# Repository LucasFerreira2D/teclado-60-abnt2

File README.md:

# Teclado 60% ABNT2 com fileira F

Teclado mecânico próprio: layout **60% ABNT2 com fileira de funções** (76 teclas), switches **hot-swap**,
**RGB por tecla + underglow + iluminação lateral**, **knob** e conector para **OLED**. O cérebro é uma
**Black Pill STM32F411** encaixada num soquete no verso da placa, pensada para rodar **QMK**.

A placa foi feita no **KiCad 10** quase toda **por script** (posicionamento, roteamento, acabamento e
correções), sem desenhar à mão no editor. Os scripts estão em [`hardware/tools/`](hardware/tools).

> **Status:** projeto da placa concluído e revisado (DRC sem erros), **ainda não fabricado**. Firmware QMK
> ainda não escrito. Pendências em [Antes de fabricar](#antes-de-fabricar).

---

## Conceito

Como o teclado deve ficar montado (esboço 3D feito antes da placa; o case ainda não existe):

| Lateral | Lateral em 3/4 |
|---|---|
|  |  |

Na lateral aparecem a cunha do case, o rasgo de RGB na altura da placa e o underglow na mesa.

- **Case em cunha** com 6° de inclinação, fechado nas laterais, e **moldura superior** que abre janelas só em
  volta de cada grupo de teclas (Esc, F1–F4, F5–F8, F9–F12, bloco principal).
- **OLED** à esquerda e **knob** à direita, na faixa acima da fileira F, rentes à moldura.
- Keycaps **perfil Cherry**, com acentos em Esc e Enter.
- **Underglow** por baixo e **rasgo de RGB nas laterais**, na altura da placa, com acrílico fosco por dentro.
- Pés traseiros dobráveis em 2 níveis.

---

## Layout

- 76 teclas: alfanumérico ABNT2 completo (`Ç`, `´`, `~`, `[`, `]`, `\`, `;`, `/`) + Esc e F1–F12.
- Enter ISO, Shift esquerdo curto (1,25u) por causa da tecla `\`.
- Sem setas nem coluna de navegação (não é 65%): setas, Del, Home/End e afins ficam numa camada no `Fn`.
- Fonte do layout: [`hardware/layout/teclado-kle.json`](hardware/layout/teclado-kle.json). Abra em
  [keyboard-layout-editor.com](http://www.keyboard-layout-editor.com) (*Raw data* → colar).

## A placa

| Frente | Verso |
|---|---|
|  |  |

Roteamento (vermelho = frente, azul = verso + plano de GND), com o acabamento das trilhas em retas e 45°:

### Especificações

| Item | Detalhe |
|---|---|
| Placa | 292 × 143 mm, 2 camadas, 1,6 mm, cantos com raio de 3 mm |
| Fixação | 10 furos M2 |
| Matriz | 6 linhas × 14 colunas, diodo 1N4148W (SOD-123) por tecla, catodo na linha |
| Switches | Cherry MX e compatíveis, soquete **Kailh hot-swap** (sem solda) |
| Estabilizadores | Cherry MX de placa: 2u (Backspace, Enter) e 6,25u (Espaço) |
| Microcontrolador | **WeAct Black Pill V3.x (STM32F411)** num soquete DIP-40, no verso |
| USB | USB-C (HRO TYPE-C-31-M-12), resistores CC de 5,1k, ESD USBLC6-2SC6, fusível de 500 mA |
| Knob | Encoder EC11 com clique (o clique entra na matriz em ROW0 × COL13) |
| Tela | Conector de 4 pinos para OLED I²C (GND, VCC, SCL, SDA) |

### Iluminação (102 LEDs endereçáveis numa cadeia só)

| Grupo | LEDs | Peça |
|---|---|---|
| Por tecla | LED1–LED76 | SK6812MINI-E, montagem reversa (brilha através do switch) |
| Underglow | LED101–LED114 | 14× SK6812MINI no verso, virados para a mesa |
| Laterais | LED201–LED212 | 12× SK6812SIDE-A na borda, apontando para fora |

Cada LED tem o próprio capacitor de 100 nF. O sinal de dados sai do STM32 (3,3 V) e passa por um
**74AHCT1G125**, que converte para 5 V antes de entrar na cadeia.

### Pinos da Black Pill usados

| Função | Pino |
|---|---|
| Dados do RGB | PA8 |
| OLED (I²C) | PB6 (SCL), PB7 (SDA) |
| Knob (A/B) | PA0, PA1 |

O mapa completo de linhas e colunas está no esquemático ([`hardware/teclado.pdf`](hardware/teclado.pdf)).

## Estrutura do repositório

```
hardware/
├── teclado.kicad_pro / .kicad_sch / .kicad_pcb   projeto KiCad 10 (abra o .kicad_pro)
├── matriz.kicad_sch, mcu.kicad_sch,
│   leds.kicad_sch, leds_extra.kicad_sch           folhas do esquemático
├── teclado.kicad_dru                              regras de DRC próprias (LED reverso, alívio térmico)
├── teclado.kicad_sym, teclado.pretty/             símbolo e footprint próprios (LED lateral)
├── teclado.pdf                                    esquemático em PDF
├── layout/teclado-kle.json                        layout no formato KLE
├── tools/                                         scripts que geraram a placa
└── REVISAO.md                                     revisão antes de fabricar
docs/img/                                          imagens deste README (geradas pelo kicad-cli)
```

## Como a placa foi feita

O fluxo inteiro roda pelo Python do KiCad (`C:\Program Files\KiCad\10.0\bin\python.exe`) e pelo
`kicad-cli`, com o KiCad fechado:

1. **Esquemático:** matriz e LEDs por teclas gerados pelo [kbplacer](https://github.com/adamws/kicad-kbplacer)
   a partir do KLE (`kbplacer.py`, `import_kbplacer.py`); folha do MCU (`gen_mcu_sheet.py`) e dos LEDs
   extras (`gen_leds_extra.py`) gerados por script.
2. **Placa:** contorno (`new_board.py`), sincronização com o esquemático sem abrir o editor (`sync_pcb.py`),
   posicionamento de switches, diodos, LEDs e estabilizadores pelo KLE (`place_keys.py`), eletrônica da faixa
   superior (`place_strip.py`), LEDs extras (`place_extra_leds.py`) e furação (`place_holes.py`).
3. **Roteamento:** exportação para o [FreeRouting](https://github.com/freerouting/freerouting) sem os planos
   de GND (`export_dsn.py`), importação do resultado e criação dos planos (`post_route.py`), fechamento das
   ligações que sobraram (`route_rest.py`, `open_pairs.py`).
4. **Acabamento:** trilhas em retas + 45° mantendo as mesmas pontas (`align45.py`), correções de DRC
   (`fix_drc.py`), ilhas de GND (`gnd_islands.py`) e costura dos planos com vias (`stitch_gnd.py`).

## Antes de fabricar

Resumo de [`hardware/REVISAO.md`](hardware/REVISAO.md):

- **OLED:** conferir a ordem dos pinos do módulo comprado (o header é GND-VCC-SCL-SDA). Invertido, o módulo
  cai em cima do USB-C.
- **LED lateral:** o footprint foi feito à mão. As funções dos pinos batem com o datasheet; o lado físico
  (espelhamento) ainda não foi confirmado.
- **Corrente:** 102 LEDs em branco total puxam ~3,7 A, e o fusível é de 500 mA. O firmware **precisa**
  limitar o brilho (~10% em branco, ~30% em efeitos coloridos).
- **Black Pill no verso:** o soquete com o módulo ocupa ~12–14 mm abaixo da placa (o case precisa dessa
  folga), e os botões BOOT0/NRST ficam para baixo: fazer a primeira gravação antes de fechar o case.
  Nunca ligar o USB do módulo e o da placa ao mesmo tempo.

## Próximos passos

- [ ] Fechar as pendências acima e gerar os Gerbers
- [ ] Fabricar e montar
- [ ] Firmware QMK (matriz, camada `Fn`, RGB com limite de corrente, knob, OLED)
- [ ] Case

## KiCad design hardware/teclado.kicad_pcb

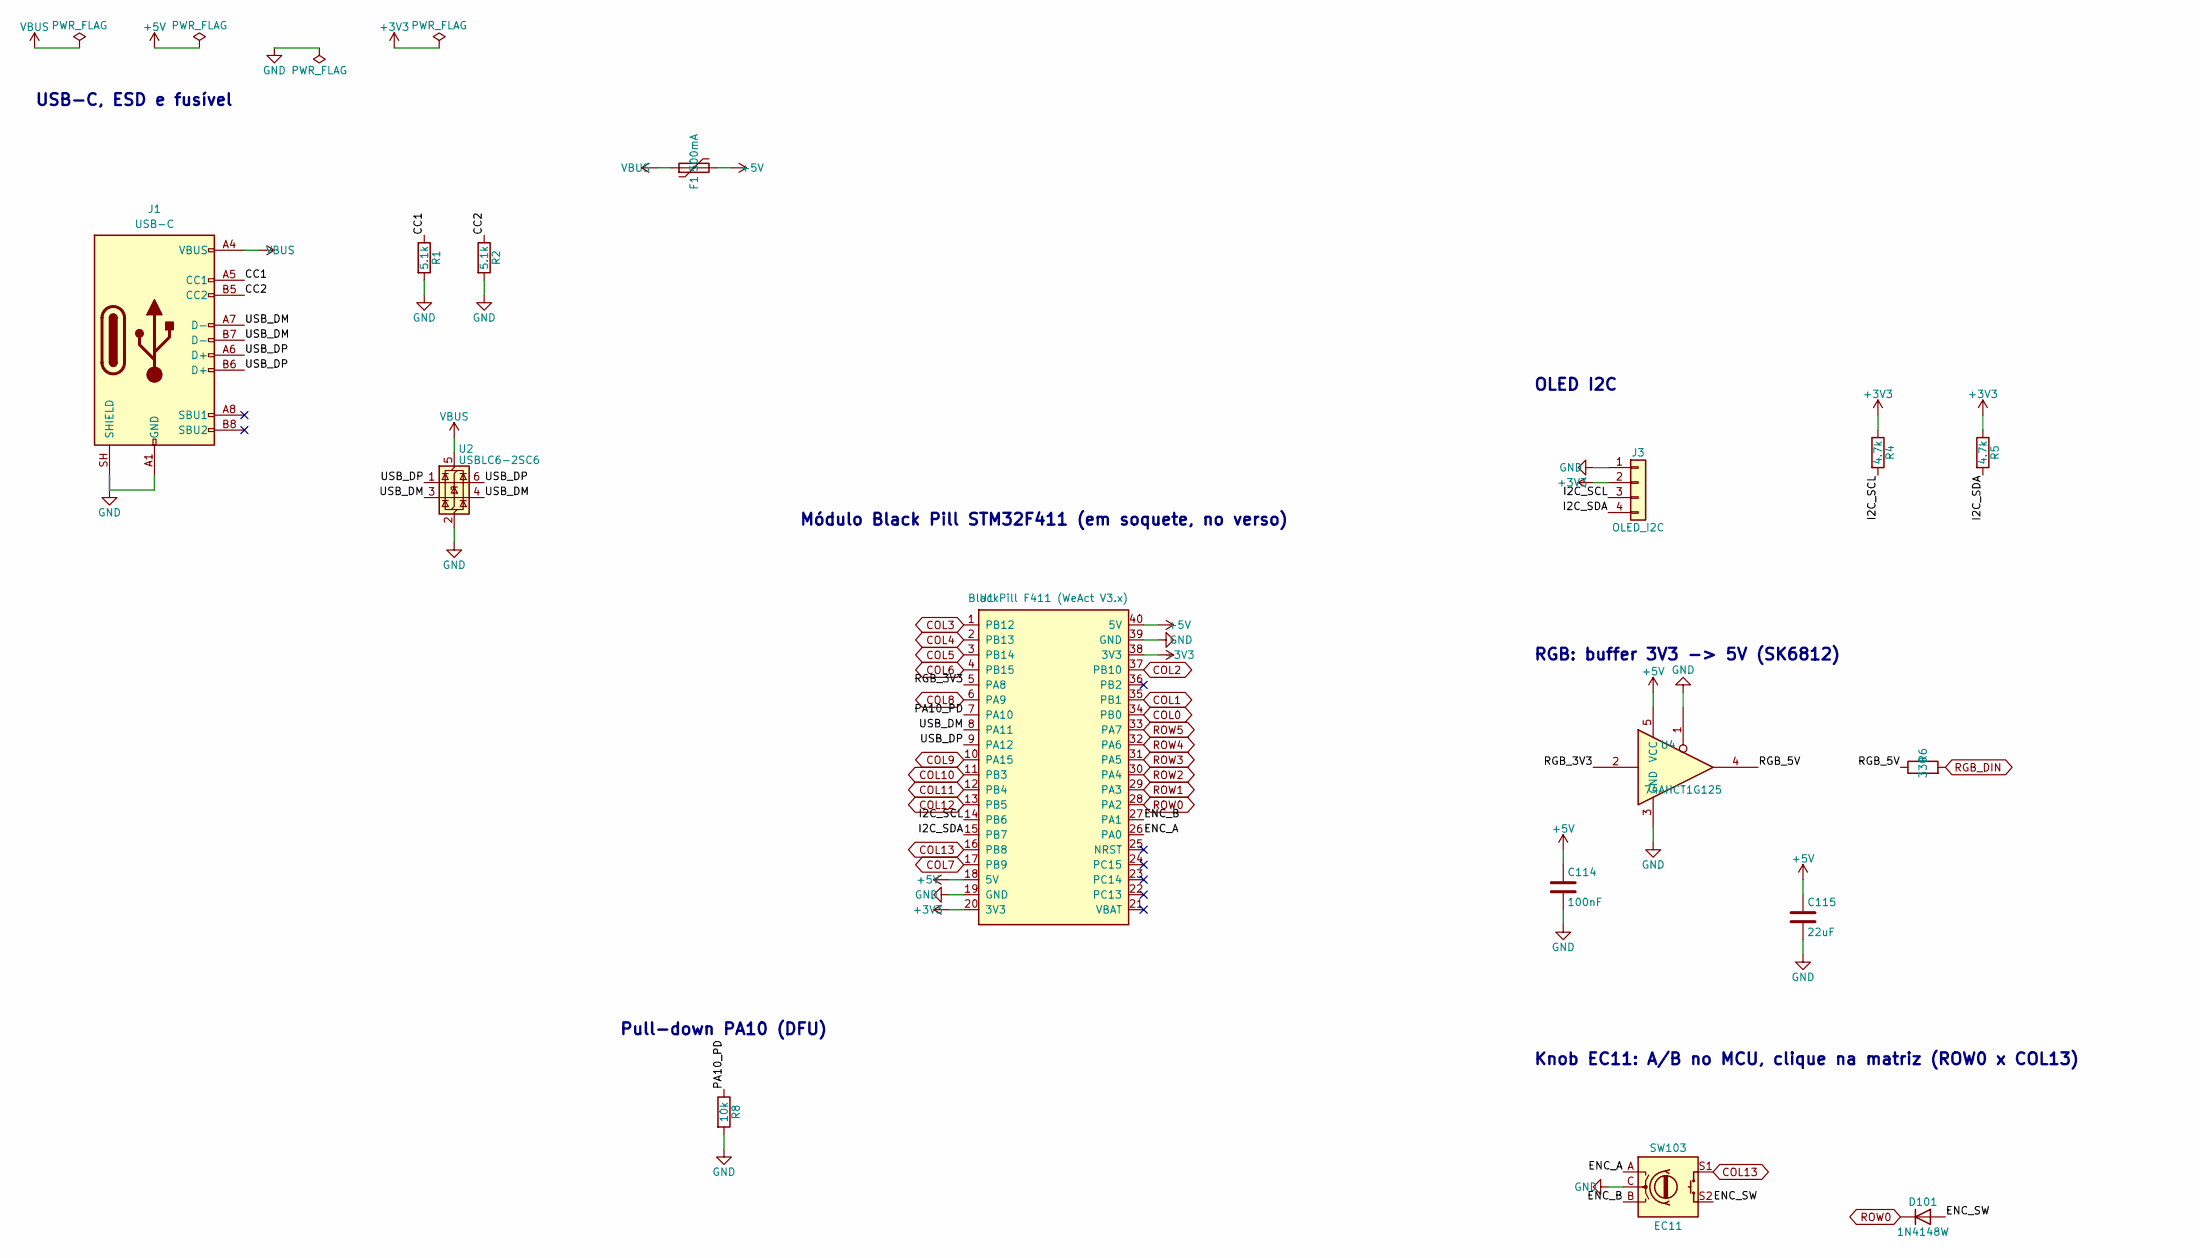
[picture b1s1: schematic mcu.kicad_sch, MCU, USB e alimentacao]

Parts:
C114: 100nF; C_0603_1608Metric
C115: 22uF; C_0805_2012Metric
D101: 1N4148W; D_SOD-123
F1: 500mA; Fuse_1206_3216Metric
J1: USB-C; USB_C_Receptacle_HRO_TYPE-C-31-M-12
J3: OLED_I2C; PinHeader_1x04_P2.54mm_Vertical
R1, R2: 5.1k; R_0603_1608Metric
R4, R5: 4.7k; R_0603_1608Metric
R6: 330; R_0603_1608Metric
R8: 10k; R_0603_1608Metric
SW103: EC11; RotaryEncoder_Alps_EC11E-Switch_Vertical_H20mm
U1: BlackPill F411 (WeAct V3.x); DIP-40_W15.24mm_Socket
U2: USBLC6-2SC6; SOT-23-6
U4: 74AHCT1G125; SOT-23-5

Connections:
+3V3: J3.2, R4.1, R5.1, U1.20 (3V3), U1.38 (3V3)
+5V: C114.1, C115.1, F1.2, U1.18 (5V), U1.40 (5V), U4.5 (VCC); also elsewhere on the board
/MCU/CC1: J1.A5 (CC1), R1.1
/MCU/CC2: J1.B5 (CC2), R2.1
/MCU/ENC_A: SW103.A, U1.26 (PA0)
/MCU/ENC_B: SW103.B, U1.27 (PA1)
/MCU/ENC_SW: D101.2 (A), SW103.S2
/MCU/I2C_SCL: J3.3, R4.2, U1.14 (PB6)
/MCU/I2C_SDA: J3.4, R5.2, U1.15 (PB7)
/MCU/PA10_PD: R8.1, U1.7 (PA10)
/MCU/RGB_3V3: U1.5 (PA8), U4.2
/MCU/RGB_5V: R6.1, U4.4
/MCU/USB_DM: J1.A7 (D-), J1.B7 (D-), U1.8 (PA11), U2.3 (I/O2), U2.4 (I/O2)
/MCU/USB_DP: J1.A6 (D+), J1.B6 (D+), U1.9 (PA12), U2.1 (I/O1), U2.6 (I/O1)
COL0: U1.34 (PB0); also elsewhere on the board
COL1: U1.35 (PB1); also elsewhere on the board
COL2: U1.37 (PB10); also elsewhere on the board
COL3: U1.1 (PB12); also elsewhere on the board
COL4: U1.2 (PB13); also elsewhere on the board
COL5: U1.3 (PB14); also elsewhere on the board
COL6: U1.4 (PB15); also elsewhere on the board
COL7: U1.17 (PB9); also elsewhere on the board
COL8: U1.6 (PA9); also elsewhere on the board
COL9: U1.10 (PA15); also elsewhere on the board
COL10: U1.11 (PB3); also elsewhere on the board
COL11: U1.12 (PB4); also elsewhere on the board
COL12: U1.13 (PB5); also elsewhere on the board
COL13: SW103.S1, U1.16 (PB8); also elsewhere on the board
GND: C114.2, C115.2, J1.A1 (GND), J1.A12 (GND), J1.B1 (GND), J1.B12 (GND), J1.SH (SHIELD), J3.1, R1.2, R2.2, R8.2, SW103.C, U1.19 (GND), U1.39 (GND), U2.2 (GND), U4.1, U4.3 (GND); also elsewhere on the board
RGB_DIN: R6.2; also elsewhere on the board
ROW0: D101.1 (K), U1.28 (PA2); also elsewhere on the board
ROW1: U1.29 (PA3); also elsewhere on the board
ROW2: U1.30 (PA4); also elsewhere on the board
ROW3: U1.31 (PA5); also elsewhere on the board
ROW4: U1.32 (PA6); also elsewhere on the board
ROW5: U1.33 (PA7); also elsewhere on the board
VBUS: F1.1, J1.A4 (VBUS), J1.A9 (VBUS), J1.B4 (VBUS), J1.B9 (VBUS), U2.5 (VBUS)

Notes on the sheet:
USB-C, ESD e fusível
Módulo Black Pill STM32F411 (em soquete, no verso)
Pull-down PA10 (DFU)
OLED I2C
RGB: buffer 3V3 -> 5V (SK6812)
Knob EC11: A/B no MCU, clique na matriz (ROW0 x COL13)

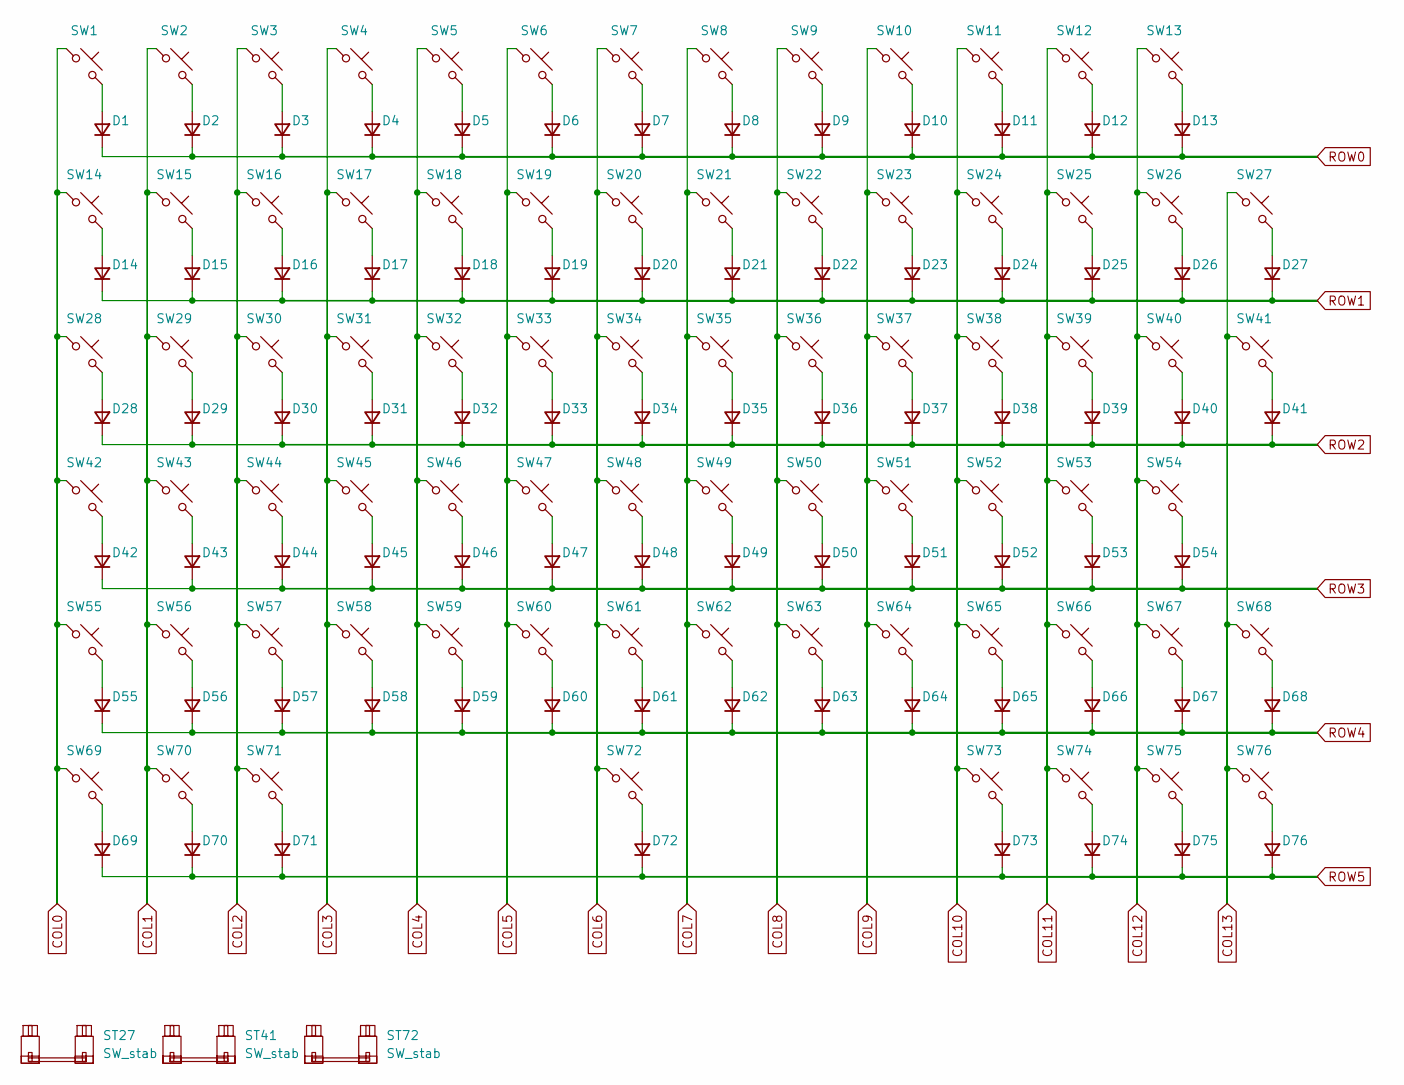
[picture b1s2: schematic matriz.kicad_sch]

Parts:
D1, D2, D3, D4, D5, D6, D7, D8, D9, D10, D11, D12, D13, D14, D15, D16, D17, D18, D19, D20, D21, D22, D23, D24, D25, D26, D27, D28, D29, D30, D31, D32, D33, D34, D35, D36, D37, D38, D39, D40, D41, D42, D43, D44, D45, D46, D47, D48, D49, D50, D51, D52, D53, D54, D55, D56, D57, D58, D59, D60, D61, D62, D63, D64, D65, D66, D67, D68, D69, D70, D71, D72, D73, D74, D75, D76: D; D_SOD-123
ST27, ST41: SW_stab; Stabilizer_Cherry_MX_2.00u
ST72: SW_stab; Stabilizer_Cherry_MX_6.25u
SW1, SW2, SW3, SW4, SW5, SW6, SW7, SW8, SW9, SW10, SW11, SW12, SW13, SW14, SW15, SW16, SW17, SW18, SW19, SW20, SW21, SW22, SW23, SW24, SW25, SW26, SW27, SW28, SW29, SW30, SW31, SW32, SW33, SW34, SW35, SW36, SW37, SW38, SW39, SW40, SW41, SW42, SW43, SW44, SW45, SW46, SW47, SW48, SW49, SW50, SW51, SW52, SW53, SW54, SW55, SW56, SW57, SW58, SW59, SW60, SW61, SW62, SW63, SW64, SW65, SW66, SW67, SW68, SW69, SW70, SW71, SW72, SW73, SW74, SW75, SW76: SW_Push; SW_Hotswap_Kailh_MX_1.00u

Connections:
COL0: SW1.1, SW14.1, SW28.1, SW42.1, SW55.1, SW69.1; also elsewhere on the board
COL1: SW2.1, SW15.1, SW29.1, SW43.1, SW56.1, SW70.1; also elsewhere on the board
COL2: SW3.1, SW16.1, SW30.1, SW44.1, SW57.1, SW71.1; also elsewhere on the board
COL3: SW4.1, SW17.1, SW31.1, SW45.1, SW58.1; also elsewhere on the board
COL4: SW5.1, SW18.1, SW32.1, SW46.1, SW59.1; also elsewhere on the board
COL5: SW6.1, SW19.1, SW33.1, SW47.1, SW60.1; also elsewhere on the board
COL6: SW7.1, SW20.1, SW34.1, SW48.1, SW61.1, SW72.1; also elsewhere on the board
COL7: SW8.1, SW21.1, SW35.1, SW49.1, SW62.1; also elsewhere on the board
COL8: SW9.1, SW22.1, SW36.1, SW50.1, SW63.1; also elsewhere on the board
COL9: SW10.1, SW23.1, SW37.1, SW51.1, SW64.1; also elsewhere on the board
COL10: SW11.1, SW24.1, SW38.1, SW52.1, SW65.1, SW73.1; also elsewhere on the board
COL11: SW12.1, SW25.1, SW39.1, SW53.1, SW66.1, SW74.1; also elsewhere on the board
COL12: SW13.1, SW26.1, SW40.1, SW54.1, SW67.1, SW75.1; also elsewhere on the board
COL13: SW27.1, SW41.1, SW68.1, SW76.1; also elsewhere on the board
unnamed: D1.2 (A), SW1.2
unnamed: D2.2 (A), SW2.2
unnamed: D3.2 (A), SW3.2
unnamed: D4.2 (A), SW4.2
unnamed: D5.2 (A), SW5.2
unnamed: D6.2 (A), SW6.2
unnamed: D7.2 (A), SW7.2
unnamed: D8.2 (A), SW8.2
unnamed: D9.2 (A), SW9.2
unnamed: D10.2 (A), SW10.2
unnamed: D11.2 (A), SW11.2
unnamed: D12.2 (A), SW12.2
unnamed: D13.2 (A), SW13.2
unnamed: D14.2 (A), SW14.2
unnamed: D15.2 (A), SW15.2
unnamed: D16.2 (A), SW16.2
unnamed: D17.2 (A), SW17.2
unnamed: D18.2 (A), SW18.2
unnamed: D19.2 (A), SW19.2
unnamed: D20.2 (A), SW20.2
unnamed: D21.2 (A), SW21.2
unnamed: D22.2 (A), SW22.2
unnamed: D23.2 (A), SW23.2
unnamed: D24.2 (A), SW24.2
unnamed: D25.2 (A), SW25.2
unnamed: D26.2 (A), SW26.2
unnamed: D27.2 (A), SW27.2
unnamed: D28.2 (A), SW28.2
unnamed: D29.2 (A), SW29.2
unnamed: D30.2 (A), SW30.2
unnamed: D31.2 (A), SW31.2
unnamed: D32.2 (A), SW32.2
unnamed: D33.2 (A), SW33.2
unnamed: D34.2 (A), SW34.2
unnamed: D35.2 (A), SW35.2
unnamed: D36.2 (A), SW36.2
unnamed: D37.2 (A), SW37.2
unnamed: D38.2 (A), SW38.2
unnamed: D39.2 (A), SW39.2
unnamed: D40.2 (A), SW40.2
unnamed: D41.2 (A), SW41.2
unnamed: D42.2 (A), SW42.2
unnamed: D43.2 (A), SW43.2
unnamed: D44.2 (A), SW44.2
unnamed: D45.2 (A), SW45.2
unnamed: D46.2 (A), SW46.2
unnamed: D47.2 (A), SW47.2
unnamed: D48.2 (A), SW48.2
unnamed: D49.2 (A), SW49.2
unnamed: D50.2 (A), SW50.2
unnamed: D51.2 (A), SW51.2
unnamed: D52.2 (A), SW52.2
unnamed: D53.2 (A), SW53.2
unnamed: D54.2 (A), SW54.2
unnamed: D55.2 (A), SW55.2
unnamed: D56.2 (A), SW56.2
unnamed: D57.2 (A), SW57.2
unnamed: D58.2 (A), SW58.2
unnamed: D59.2 (A), SW59.2
unnamed: D60.2 (A), SW60.2
unnamed: D61.2 (A), SW61.2
unnamed: D62.2 (A), SW62.2
unnamed: D63.2 (A), SW63.2
unnamed: D64.2 (A), SW64.2
unnamed: D65.2 (A), SW65.2
unnamed: D66.2 (A), SW66.2
unnamed: D67.2 (A), SW67.2
unnamed: D68.2 (A), SW68.2
unnamed: D69.2 (A), SW69.2
unnamed: D70.2 (A), SW70.2
unnamed: D71.2 (A), SW71.2
unnamed: D72.2 (A), SW72.2
unnamed: D73.2 (A), SW73.2
unnamed: D74.2 (A), SW74.2
unnamed: D75.2 (A), SW75.2
unnamed: D76.2 (A), SW76.2
ROW0: D1.1 (K), D2.1 (K), D3.1 (K), D4.1 (K), D5.1 (K), D6.1 (K), D7.1 (K), D8.1 (K), D9.1 (K), D10.1 (K), D11.1 (K), D12.1 (K), D13.1 (K); also elsewhere on the board
ROW1: D14.1 (K), D15.1 (K), D16.1 (K), D17.1 (K), D18.1 (K), D19.1 (K), D20.1 (K), D21.1 (K), D22.1 (K), D23.1 (K), D24.1 (K), D25.1 (K), D26.1 (K), D27.1 (K); also elsewhere on the board
ROW2: D28.1 (K), D29.1 (K), D30.1 (K), D31.1 (K), D32.1 (K), D33.1 (K), D34.1 (K), D35.1 (K), D36.1 (K), D37.1 (K), D38.1 (K), D39.1 (K), D40.1 (K), D41.1 (K); also elsewhere on the board
ROW3: D42.1 (K), D43.1 (K), D44.1 (K), D45.1 (K), D46.1 (K), D47.1 (K), D48.1 (K), D49.1 (K), D50.1 (K), D51.1 (K), D52.1 (K), D53.1 (K), D54.1 (K); also elsewhere on the board
ROW4: D55.1 (K), D56.1 (K), D57.1 (K), D58.1 (K), D59.1 (K), D60.1 (K), D61.1 (K), D62.1 (K), D63.1 (K), D64.1 (K), D65.1 (K), D66.1 (K), D67.1 (K), D68.1 (K); also elsewhere on the board
ROW5: D69.1 (K), D70.1 (K), D71.1 (K), D72.1 (K), D73.1 (K), D74.1 (K), D75.1 (K), D76.1 (K); also elsewhere on the board

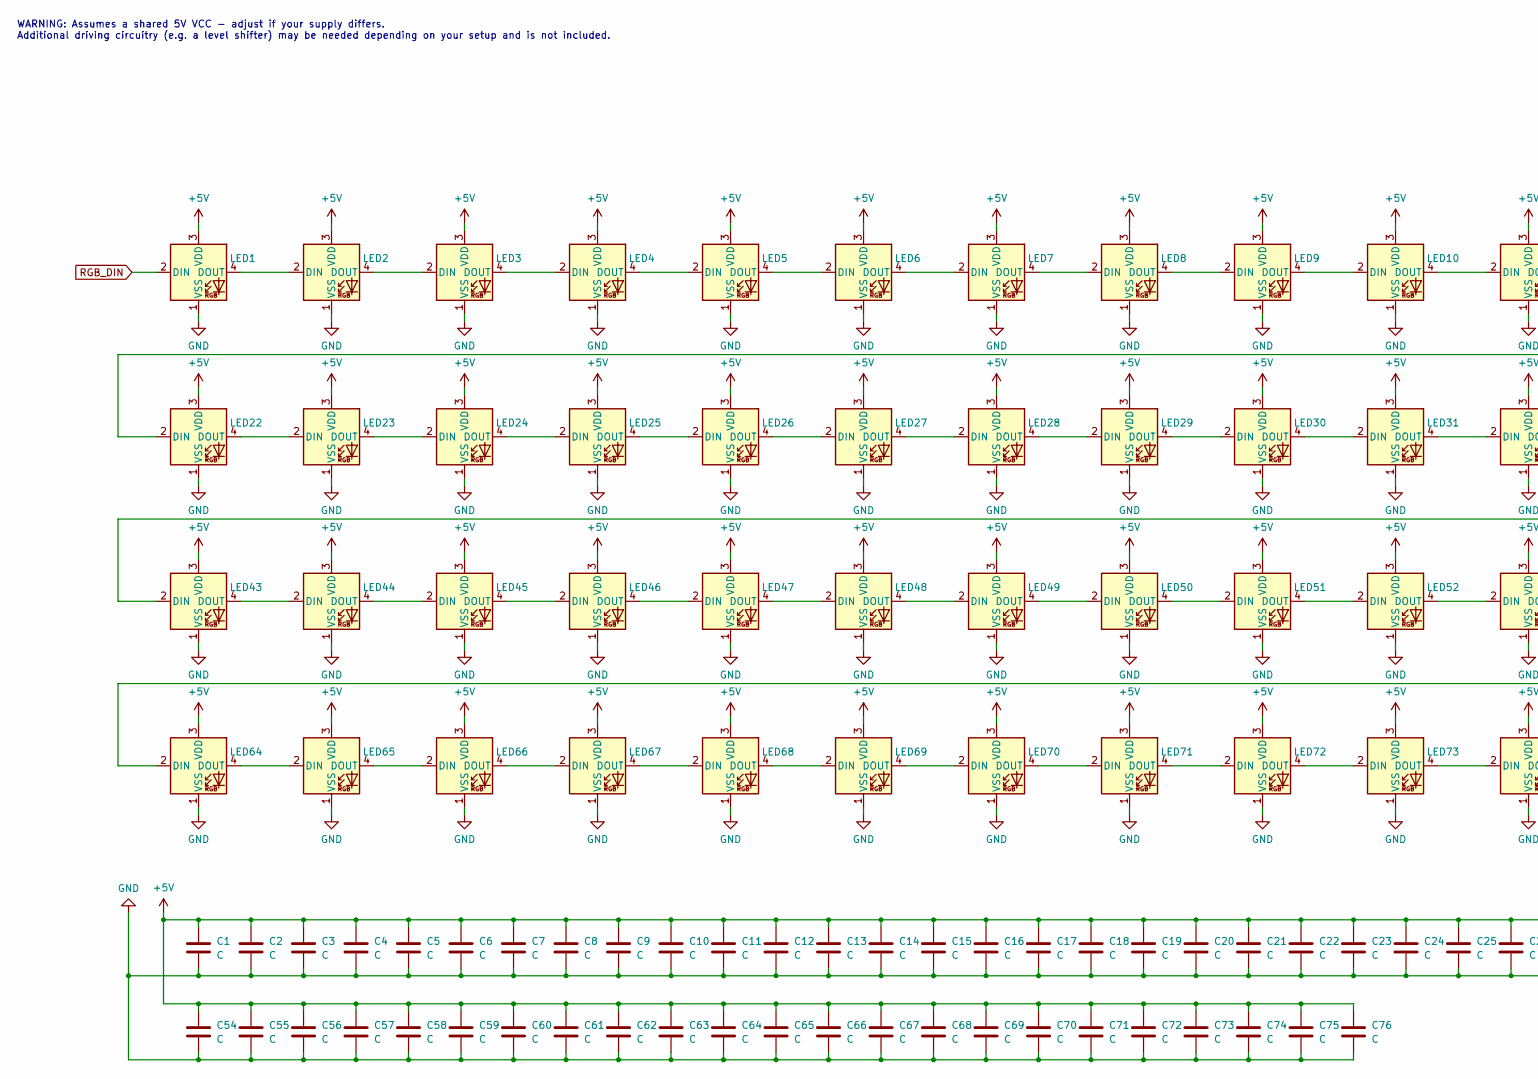
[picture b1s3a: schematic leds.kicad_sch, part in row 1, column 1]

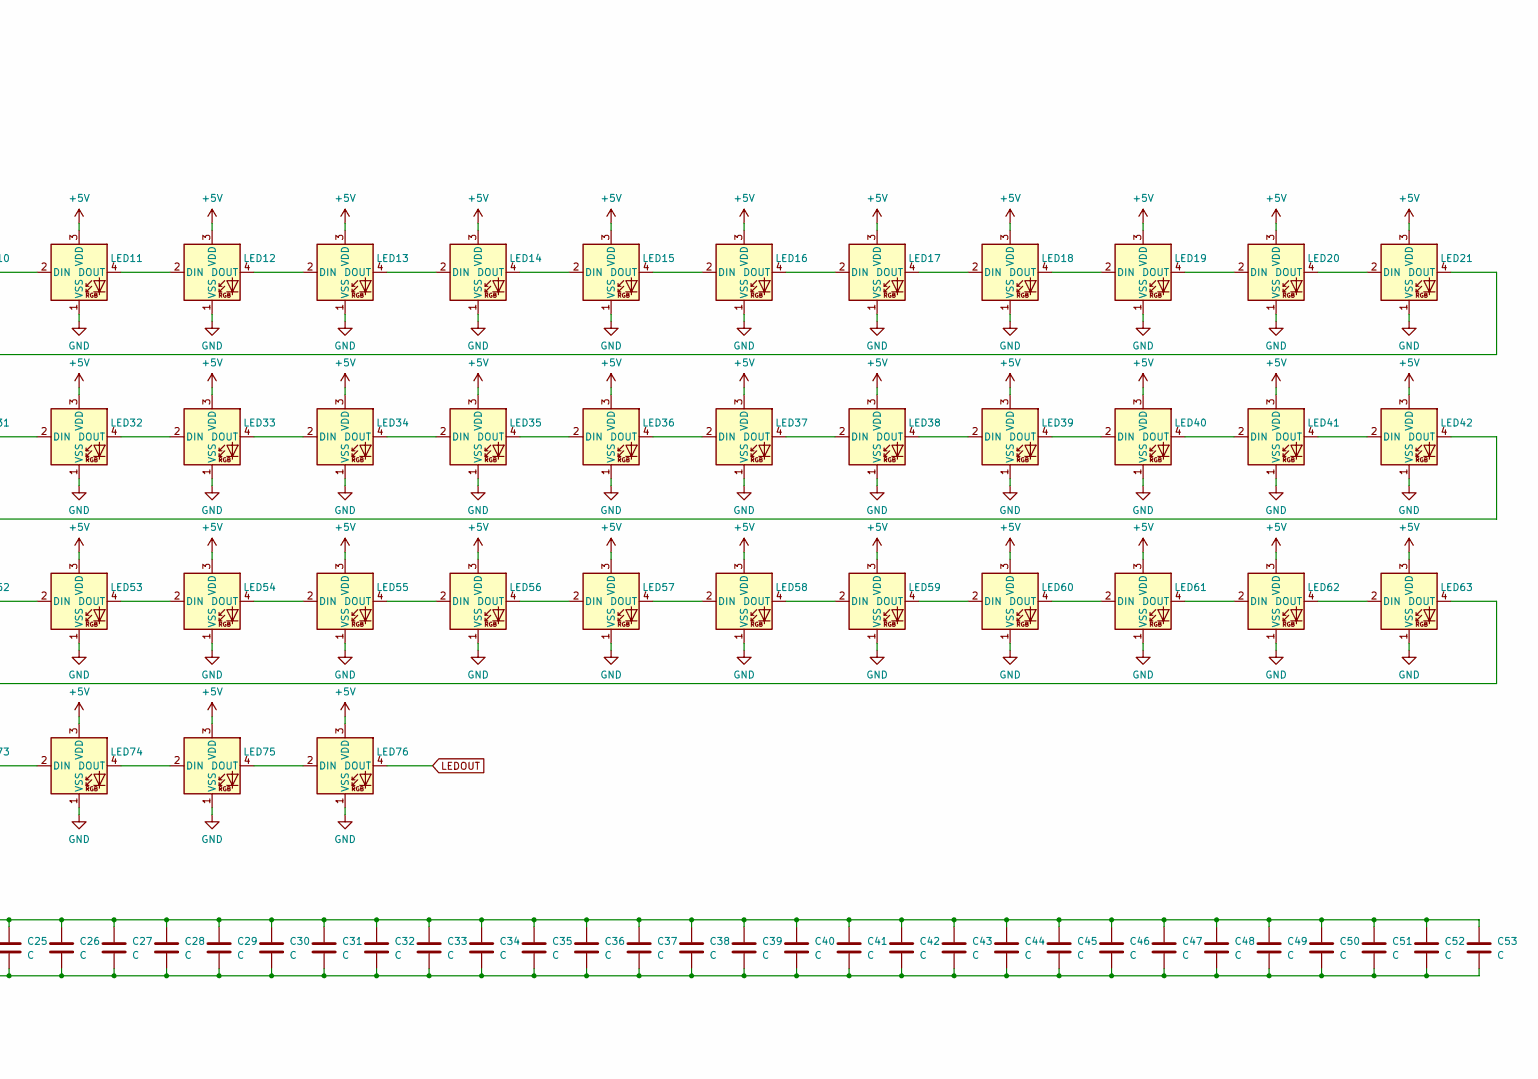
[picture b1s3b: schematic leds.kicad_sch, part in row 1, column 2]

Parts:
C1, C2, C3, C4, C5, C6, C7, C8, C9, C10, C11, C12, C13, C14, C15, C16, C17, C18, C19, C20, C21, C22, C23, C24, C25, C26, C27, C28, C29, C30, C31, C32, C33, C34, C35, C36, C37, C38, C39, C40, C41, C42, C43, C44, C45, C46, C47, C48, C49, C50, C51, C52, C53, C54, C55, C56, C57, C58, C59, C60, C61, C62, C63, C64, C65, C66, C67, C68, C69, C70, C71, C72, C73, C74, C75, C76: C; C_0603_1608Metric
LED1, LED2, LED3, LED4, LED5, LED6, LED7, LED8, LED9, LED10, LED11, LED12, LED13, LED14, LED15, LED16, LED17, LED18, LED19, LED20, LED21, LED22, LED23, LED24, LED25, LED26, LED27, LED28, LED29, LED30, LED31, LED32, LED33, LED34, LED35, LED36, LED37, LED38, LED39, LED40, LED41, LED42, LED43, LED44, LED45, LED46, LED47, LED48, LED49, LED50, LED51, LED52, LED53, LED54, LED55, LED56, LED57, LED58, LED59, LED60, LED61, LED62, LED63, LED64, LED65, LED66, LED67, LED68, LED69, LED70, LED71, LED72, LED73, LED74, LED75, LED76: SK6812MINI-E; LED_SK6812MINI-E_3.2x2.8mm_P1.5mm_ReverseMount

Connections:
+5V: C1.1, C2.1, C3.1, C4.1, C5.1, C6.1, C7.1, C8.1, C9.1, C10.1, C11.1, C12.1, C13.1, C14.1, C15.1, C16.1, C17.1, C18.1, C19.1, C20.1, C21.1, C22.1, C23.1, C24.1, C25.1, C26.1, C27.1, C28.1, C29.1, C30.1, C31.1, C32.1, C33.1, C34.1, C35.1, C36.1, C37.1, C38.1, C39.1, C40.1, C41.1, C42.1, C43.1, C44.1, C45.1, C46.1, C47.1, C48.1, C49.1, C50.1, C51.1, C52.1, C53.1, C54.1, C55.1, C56.1, C57.1, C58.1, C59.1, C60.1, C61.1, C62.1, C63.1, C64.1, C65.1, C66.1, C67.1, C68.1, C69.1, C70.1, C71.1, C72.1, C73.1, C74.1, C75.1, C76.1, LED1.3 (VDD), LED2.3 (VDD), LED3.3 (VDD), LED4.3 (VDD), LED5.3 (VDD), LED6.3 (VDD), LED7.3 (VDD), LED8.3 (VDD), LED9.3 (VDD), LED10.3 (VDD), LED11.3 (VDD), LED12.3 (VDD), LED13.3 (VDD), LED14.3 (VDD), LED15.3 (VDD), LED16.3 (VDD), LED17.3 (VDD), LED18.3 (VDD), LED19.3 (VDD), LED20.3 (VDD), LED21.3 (VDD), LED22.3 (VDD), LED23.3 (VDD), LED24.3 (VDD), LED25.3 (VDD), LED26.3 (VDD), LED27.3 (VDD), LED28.3 (VDD), LED29.3 (VDD), LED30.3 (VDD), LED31.3 (VDD), LED32.3 (VDD), LED33.3 (VDD), LED34.3 (VDD), LED35.3 (VDD), LED36.3 (VDD), LED37.3 (VDD), LED38.3 (VDD), LED39.3 (VDD), LED40.3 (VDD), LED41.3 (VDD), LED42.3 (VDD), LED43.3 (VDD), LED44.3 (VDD), LED45.3 (VDD), LED46.3 (VDD), LED47.3 (VDD), LED48.3 (VDD), LED49.3 (VDD), LED50.3 (VDD), LED51.3 (VDD), LED52.3 (VDD), LED53.3 (VDD), LED54.3 (VDD), LED55.3 (VDD), LED56.3 (VDD), LED57.3 (VDD), LED58.3 (VDD), LED59.3 (VDD), LED60.3 (VDD), LED61.3 (VDD), LED62.3 (VDD), LED63.3 (VDD), LED64.3 (VDD), LED65.3 (VDD), LED66.3 (VDD), LED67.3 (VDD), LED68.3 (VDD), LED69.3 (VDD), LED70.3 (VDD), LED71.3 (VDD), LED72.3 (VDD), LED73.3 (VDD), LED74.3 (VDD), LED75.3 (VDD), LED76.3 (VDD); also elsewhere on the board
GND: C1.2, C2.2, C3.2, C4.2, C5.2, C6.2, C7.2, C8.2, C9.2, C10.2, C11.2, C12.2, C13.2, C14.2, C15.2, C16.2, C17.2, C18.2, C19.2, C20.2, C21.2, C22.2, C23.2, C24.2, C25.2, C26.2, C27.2, C28.2, C29.2, C30.2, C31.2, C32.2, C33.2, C34.2, C35.2, C36.2, C37.2, C38.2, C39.2, C40.2, C41.2, C42.2, C43.2, C44.2, C45.2, C46.2, C47.2, C48.2, C49.2, C50.2, C51.2, C52.2, C53.2, C54.2, C55.2, C56.2, C57.2, C58.2, C59.2, C60.2, C61.2, C62.2, C63.2, C64.2, C65.2, C66.2, C67.2, C68.2, C69.2, C70.2, C71.2, C72.2, C73.2, C74.2, C75.2, C76.2, LED1.1 (VSS), LED2.1 (VSS), LED3.1 (VSS), LED4.1 (VSS), LED5.1 (VSS), LED6.1 (VSS), LED7.1 (VSS), LED8.1 (VSS), LED9.1 (VSS), LED10.1 (VSS), LED11.1 (VSS), LED12.1 (VSS), LED13.1 (VSS), LED14.1 (VSS), LED15.1 (VSS), LED16.1 (VSS), LED17.1 (VSS), LED18.1 (VSS), LED19.1 (VSS), LED20.1 (VSS), LED21.1 (VSS), LED22.1 (VSS), LED23.1 (VSS), LED24.1 (VSS), LED25.1 (VSS), LED26.1 (VSS), LED27.1 (VSS), LED28.1 (VSS), LED29.1 (VSS), LED30.1 (VSS), LED31.1 (VSS), LED32.1 (VSS), LED33.1 (VSS), LED34.1 (VSS), LED35.1 (VSS), LED36.1 (VSS), LED37.1 (VSS), LED38.1 (VSS), LED39.1 (VSS), LED40.1 (VSS), LED41.1 (VSS), LED42.1 (VSS), LED43.1 (VSS), LED44.1 (VSS), LED45.1 (VSS), LED46.1 (VSS), LED47.1 (VSS), LED48.1 (VSS), LED49.1 (VSS), LED50.1 (VSS), LED51.1 (VSS), LED52.1 (VSS), LED53.1 (VSS), LED54.1 (VSS), LED55.1 (VSS), LED56.1 (VSS), LED57.1 (VSS), LED58.1 (VSS), LED59.1 (VSS), LED60.1 (VSS), LED61.1 (VSS), LED62.1 (VSS), LED63.1 (VSS), LED64.1 (VSS), LED65.1 (VSS), LED66.1 (VSS), LED67.1 (VSS), LED68.1 (VSS), LED69.1 (VSS), LED70.1 (VSS), LED71.1 (VSS), LED72.1 (VSS), LED73.1 (VSS), LED74.1 (VSS), LED75.1 (VSS), LED76.1 (VSS); also elsewhere on the board
LEDOUT: LED76.4 (DOUT); also elsewhere on the board
unnamed: LED1.4 (DOUT), LED2.2 (DIN)
unnamed: LED2.4 (DOUT), LED3.2 (DIN)
unnamed: LED3.4 (DOUT), LED4.2 (DIN)
unnamed: LED4.4 (DOUT), LED5.2 (DIN)
unnamed: LED5.4 (DOUT), LED6.2 (DIN)
unnamed: LED6.4 (DOUT), LED7.2 (DIN)
unnamed: LED7.4 (DOUT), LED8.2 (DIN)
unnamed: LED8.4 (DOUT), LED9.2 (DIN)
unnamed: LED9.4 (DOUT), LED10.2 (DIN)
unnamed: LED10.4 (DOUT), LED11.2 (DIN)
unnamed: LED11.4 (DOUT), LED12.2 (DIN)
unnamed: LED12.4 (DOUT), LED13.2 (DIN)
unnamed: LED13.4 (DOUT), LED14.2 (DIN)
unnamed: LED14.4 (DOUT), LED15.2 (DIN)
unnamed: LED15.4 (DOUT), LED16.2 (DIN)
unnamed: LED16.4 (DOUT), LED17.2 (DIN)
unnamed: LED17.4 (DOUT), LED18.2 (DIN)
unnamed: LED18.4 (DOUT), LED19.2 (DIN)
unnamed: LED19.4 (DOUT), LED20.2 (DIN)
unnamed: LED20.4 (DOUT), LED21.2 (DIN)
unnamed: LED21.4 (DOUT), LED22.2 (DIN)
unnamed: LED22.4 (DOUT), LED23.2 (DIN)
unnamed: LED23.4 (DOUT), LED24.2 (DIN)
unnamed: LED24.4 (DOUT), LED25.2 (DIN)
unnamed: LED25.4 (DOUT), LED26.2 (DIN)
unnamed: LED26.4 (DOUT), LED27.2 (DIN)
unnamed: LED27.4 (DOUT), LED28.2 (DIN)
unnamed: LED28.4 (DOUT), LED29.2 (DIN)
unnamed: LED29.4 (DOUT), LED30.2 (DIN)
unnamed: LED30.4 (DOUT), LED31.2 (DIN)
unnamed: LED31.4 (DOUT), LED32.2 (DIN)
unnamed: LED32.4 (DOUT), LED33.2 (DIN)
unnamed: LED33.4 (DOUT), LED34.2 (DIN)
unnamed: LED34.4 (DOUT), LED35.2 (DIN)
unnamed: LED35.4 (DOUT), LED36.2 (DIN)
unnamed: LED36.4 (DOUT), LED37.2 (DIN)
unnamed: LED37.4 (DOUT), LED38.2 (DIN)
unnamed: LED38.4 (DOUT), LED39.2 (DIN)
unnamed: LED39.4 (DOUT), LED40.2 (DIN)
unnamed: LED40.4 (DOUT), LED41.2 (DIN)
unnamed: LED41.4 (DOUT), LED42.2 (DIN)
unnamed: LED42.4 (DOUT), LED43.2 (DIN)
unnamed: LED43.4 (DOUT), LED44.2 (DIN)
unnamed: LED44.4 (DOUT), LED45.2 (DIN)
unnamed: LED45.4 (DOUT), LED46.2 (DIN)
unnamed: LED46.4 (DOUT), LED47.2 (DIN)
unnamed: LED47.4 (DOUT), LED48.2 (DIN)
unnamed: LED48.4 (DOUT), LED49.2 (DIN)
unnamed: LED49.4 (DOUT), LED50.2 (DIN)
unnamed: LED50.4 (DOUT), LED51.2 (DIN)
unnamed: LED51.4 (DOUT), LED52.2 (DIN)
unnamed: LED52.4 (DOUT), LED53.2 (DIN)
unnamed: LED53.4 (DOUT), LED54.2 (DIN)
unnamed: LED54.4 (DOUT), LED55.2 (DIN)
unnamed: LED55.4 (DOUT), LED56.2 (DIN)
unnamed: LED56.4 (DOUT), LED57.2 (DIN)
unnamed: LED57.4 (DOUT), LED58.2 (DIN)
unnamed: LED58.4 (DOUT), LED59.2 (DIN)
unnamed: LED59.4 (DOUT), LED60.2 (DIN)
unnamed: LED60.4 (DOUT), LED61.2 (DIN)
unnamed: LED61.4 (DOUT), LED62.2 (DIN)
unnamed: LED62.4 (DOUT), LED63.2 (DIN)
unnamed: LED63.4 (DOUT), LED64.2 (DIN)
unnamed: LED64.4 (DOUT), LED65.2 (DIN)
unnamed: LED65.4 (DOUT), LED66.2 (DIN)
unnamed: LED66.4 (DOUT), LED67.2 (DIN)
unnamed: LED67.4 (DOUT), LED68.2 (DIN)
unnamed: LED68.4 (DOUT), LED69.2 (DIN)
unnamed: LED69.4 (DOUT), LED70.2 (DIN)
unnamed: LED70.4 (DOUT), LED71.2 (DIN)
unnamed: LED71.4 (DOUT), LED72.2 (DIN)
unnamed: LED72.4 (DOUT), LED73.2 (DIN)
unnamed: LED73.4 (DOUT), LED74.2 (DIN)
unnamed: LED74.4 (DOUT), LED75.2 (DIN)
unnamed: LED75.4 (DOUT), LED76.2 (DIN)
RGB_DIN: LED1.2 (DIN); also elsewhere on the board

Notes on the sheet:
WARNING: Assumes a shared 5V VCC - adjust if your supply differs. Additional driving circuitry (e.g. a level shifter) may be needed depending on your setup and is not included.

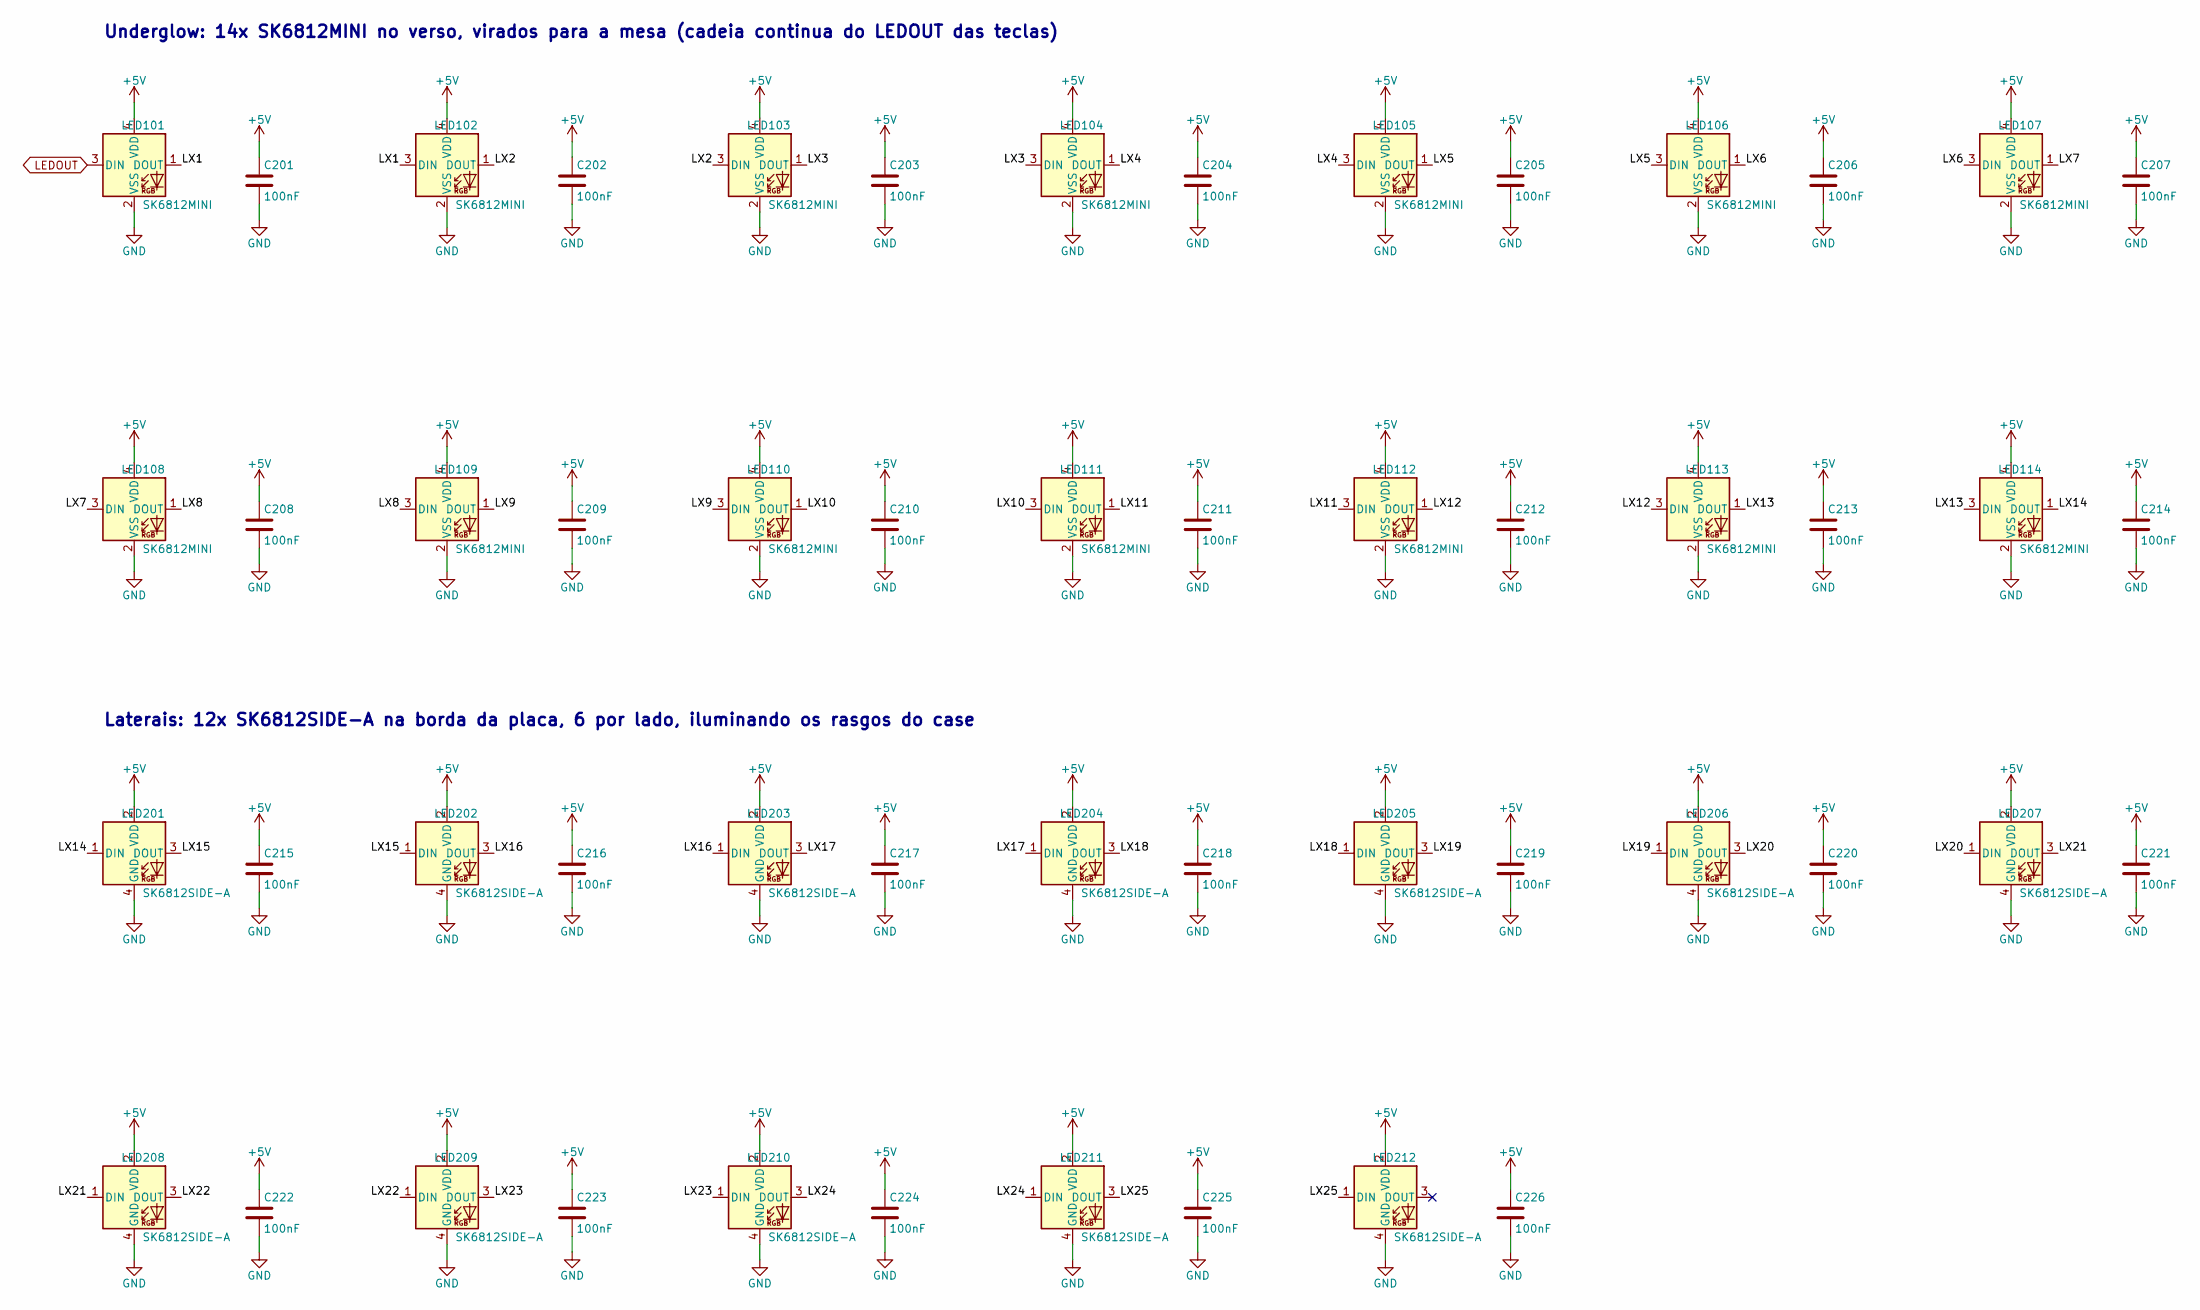
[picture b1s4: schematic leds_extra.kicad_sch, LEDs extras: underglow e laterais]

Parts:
C201, C202, C203, C204, C205, C206, C207, C208, C209, C210, C211, C212, C213, C214, C215, C216, C217, C218, C219, C220, C221, C222, C223, C224, C225, C226: 100nF; C_0603_1608Metric
LED101, LED102, LED103, LED104, LED105, LED106, LED107, LED108, LED109, LED110, LED111, LED112, LED113, LED114: SK6812MINI; LED_SK6812MINI_PLCC4_3.5x3.5mm_P1.75mm
LED201, LED202, LED203, LED204, LED205, LED206, LED207, LED208, LED209, LED210, LED211, LED212: SK6812SIDE-A; LED_SK6812SIDE-A_4.0x1.6mm

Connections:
+5V: C201.1, C202.1, C203.1, C204.1, C205.1, C206.1, C207.1, C208.1, C209.1, C210.1, C211.1, C212.1, C213.1, C214.1, C215.1, C216.1, C217.1, C218.1, C219.1, C220.1, C221.1, C222.1, C223.1, C224.1, C225.1, C226.1, LED101.4 (VDD), LED102.4 (VDD), LED103.4 (VDD), LED104.4 (VDD), LED105.4 (VDD), LED106.4 (VDD), LED107.4 (VDD), LED108.4 (VDD), LED109.4 (VDD), LED110.4 (VDD), LED111.4 (VDD), LED112.4 (VDD), LED113.4 (VDD), LED114.4 (VDD), LED201.2 (VDD), LED202.2 (VDD), LED203.2 (VDD), LED204.2 (VDD), LED205.2 (VDD), LED206.2 (VDD), LED207.2 (VDD), LED208.2 (VDD), LED209.2 (VDD), LED210.2 (VDD), LED211.2 (VDD), LED212.2 (VDD); also elsewhere on the board
/LEDs extras/LX1: LED101.1 (DOUT), LED102.3 (DIN)
/LEDs extras/LX2: LED102.1 (DOUT), LED103.3 (DIN)
/LEDs extras/LX3: LED103.1 (DOUT), LED104.3 (DIN)
/LEDs extras/LX4: LED104.1 (DOUT), LED105.3 (DIN)
/LEDs extras/LX5: LED105.1 (DOUT), LED106.3 (DIN)
/LEDs extras/LX6: LED106.1 (DOUT), LED107.3 (DIN)
/LEDs extras/LX7: LED107.1 (DOUT), LED108.3 (DIN)
/LEDs extras/LX8: LED108.1 (DOUT), LED109.3 (DIN)
/LEDs extras/LX9: LED109.1 (DOUT), LED110.3 (DIN)
/LEDs extras/LX10: LED110.1 (DOUT), LED111.3 (DIN)
/LEDs extras/LX11: LED111.1 (DOUT), LED112.3 (DIN)
/LEDs extras/LX12: LED112.1 (DOUT), LED113.3 (DIN)
/LEDs extras/LX13: LED113.1 (DOUT), LED114.3 (DIN)
/LEDs extras/LX14: LED114.1 (DOUT), LED201.1 (DIN)
/LEDs extras/LX15: LED201.3 (DOUT), LED202.1 (DIN)
/LEDs extras/LX16: LED202.3 (DOUT), LED203.1 (DIN)
/LEDs extras/LX17: LED203.3 (DOUT), LED204.1 (DIN)
/LEDs extras/LX18: LED204.3 (DOUT), LED205.1 (DIN)
/LEDs extras/LX19: LED205.3 (DOUT), LED206.1 (DIN)
/LEDs extras/LX20: LED206.3 (DOUT), LED207.1 (DIN)
/LEDs extras/LX21: LED207.3 (DOUT), LED208.1 (DIN)
/LEDs extras/LX22: LED208.3 (DOUT), LED209.1 (DIN)
/LEDs extras/LX23: LED209.3 (DOUT), LED210.1 (DIN)
/LEDs extras/LX24: LED210.3 (DOUT), LED211.1 (DIN)
/LEDs extras/LX25: LED211.3 (DOUT), LED212.1 (DIN)
GND: C201.2, C202.2, C203.2, C204.2, C205.2, C206.2, C207.2, C208.2, C209.2, C210.2, C211.2, C212.2, C213.2, C214.2, C215.2, C216.2, C217.2, C218.2, C219.2, C220.2, C221.2, C222.2, C223.2, C224.2, C225.2, C226.2, LED101.2 (VSS), LED102.2 (VSS), LED103.2 (VSS), LED104.2 (VSS), LED105.2 (VSS), LED106.2 (VSS), LED107.2 (VSS), LED108.2 (VSS), LED109.2 (VSS), LED110.2 (VSS), LED111.2 (VSS), LED112.2 (VSS), LED113.2 (VSS), LED114.2 (VSS), LED201.4 (GND), LED202.4 (GND), LED203.4 (GND), LED204.4 (GND), LED205.4 (GND), LED206.4 (GND), LED207.4 (GND), LED208.4 (GND), LED209.4 (GND), LED210.4 (GND), LED211.4 (GND), LED212.4 (GND); also elsewhere on the board
LEDOUT: LED101.3 (DIN); also elsewhere on the board

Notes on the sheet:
Underglow: 14x SK6812MINI no verso, virados para a mesa (cadeia continua do LEDOUT das teclas)
Laterais: 12x SK6812SIDE-A na borda da placa, 6 por lado, iluminando os rasgos do case
